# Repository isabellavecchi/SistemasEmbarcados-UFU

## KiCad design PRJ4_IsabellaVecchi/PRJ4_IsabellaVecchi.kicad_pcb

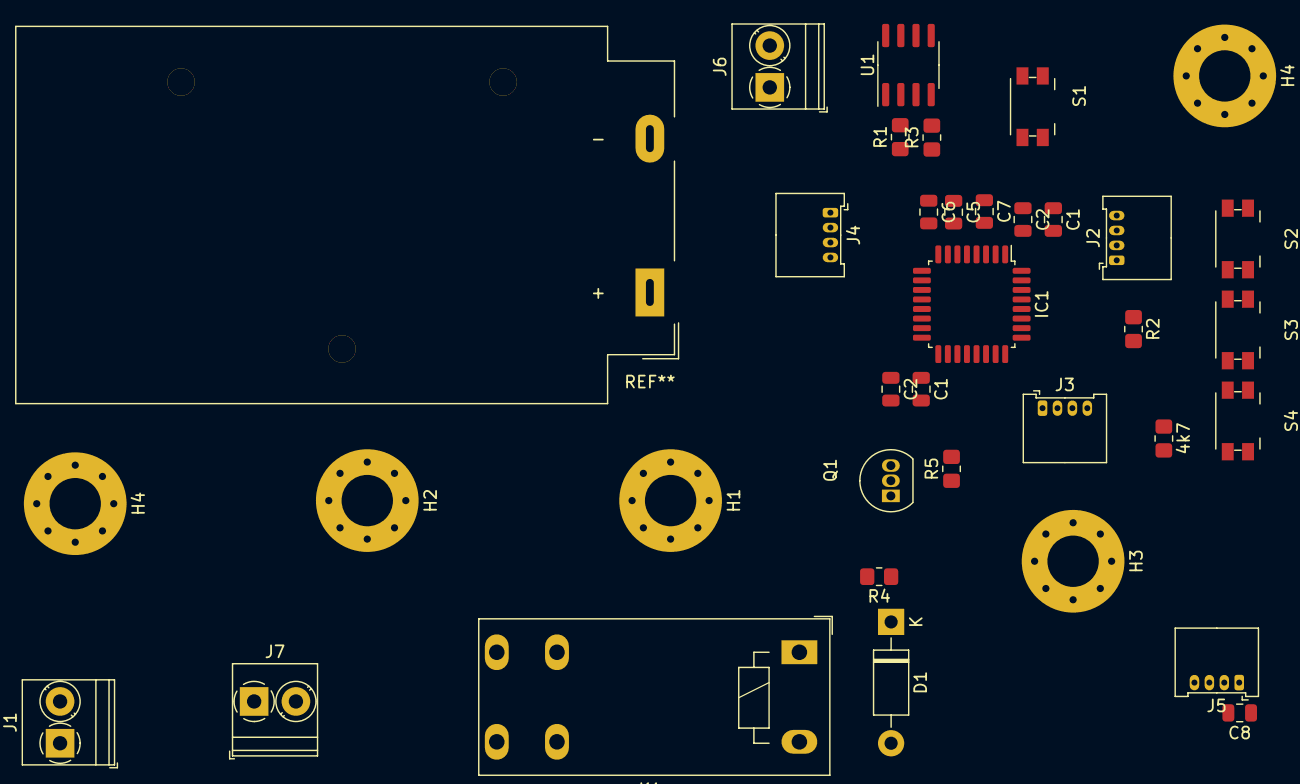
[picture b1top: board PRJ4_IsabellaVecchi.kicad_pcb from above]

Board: 2 copper layers, 35 parts (0 on the bottom side), 21 nets, no tracks yet.

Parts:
4k7: SMD R; R_0805_2012Metric_Pad1.20x1.40mm_HandSolder
C1, C1#2: 10uF; C_0805_2012Metric
C2, C2#2: 100nF; C_0805_2012Metric
C5: 1uf; C_0805_2012Metric
C6: 100nf; C_0805_2012Metric
C7: 0.1uf; C_0805_2012Metric
C8: 100n; C_0805_2012Metric
D1: 1N4001; D_DO-41_SOD81_P10.16mm_Horizontal
H1, H2, H3, H4, H4#2: MountingHole_Pad; MountingHole_4.3mm_M4_Pad_Via
IC1: STM32L052K8T6; LQFP-32_7x7mm_P0.8mm
J1: TerminalBateria; TerminalBlock_Phoenix_PT-1,5-2-3.5-H_1x02_P3.50mm_Horizontal
J2: Display_OLed; Molex_PicoBlade_53048-0410_1x04_P1.25mm_Horizontal
J3: ST-Link; Molex_PicoBlade_53048-0410_1x04_P1.25mm_Horizontal
J4: Terminal_SensorUmidadeTerra; Molex_PicoBlade_53048-0410_1x04_P1.25mm_Horizontal
J5: Terminal_SensorAmbiente; Molex_PicoBlade_53048-0410_1x04_P1.25mm_Horizontal
J6: TerminalPilha; TerminalBlock_Phoenix_PT-1,5-2-3.5-H_1x02_P3.50mm_Horizontal
J7: Válvula Solenoide; TerminalBlock_Phoenix_PT-1,5-2-3.5-H_1x02_P3.50mm_Horizontal
K1: RT44xxxx; Relay_DPST_Schrack-RT2-FormA_RM5mm
Q1: pnp TO-92 BC307; TO-92_Inline
R1: SMD 220R; R_0805_2012Metric_Pad1.20x1.40mm_HandSolder
R2: 10kR; R_0805_2012Metric_Pad1.20x1.40mm_HandSolder
R3: SMD 361R; R_0805_2012Metric_Pad1.20x1.40mm_HandSolder
R4, R5: SMD R; R_0805_2012Metric_Pad1.20x1.40mm_HandSolder
S1, S2, S3, S4: btSwitch; Panasonic_EVQPUK_EVQPUB
U1: LM317L_SO8; SOIC-8_3.9x4.9mm_P1.27mm

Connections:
5V: J6.1, U1.1 (VI)
12V: J1.1, K1.14, K1.24
BOOT0: IC1.31 (BOOT0), R2.1
BtMais: IC1.28 (PB5), S2.2 (COM)
D0-A: IC1.19 (PA9), J5.3 (D0)
D0-T: IC1.8 (PA2), J4.3 (D0)
Dp_SCL: IC1.29 (PB6), J2.3 (SCL)
Dp_SDA: IC1.30 (PB7), J2.4 (SDA)
GND: C1.2, C2#2.2, C5.2, C6.2
GND_bat: J1.2, J7.2
NRST: C7.2, IC1.4 (NRST)
unnamed: D1.2 (A), K1.A2, Q1.1 (C)
unnamed: D1.1 (K), K1.A1, R4.1
unnamed: J7.1, K1.11
unnamed: R1.1, R3.2, U1.4 (ADJ)
ST_SCL: IC1.24 (PA14), J3.3 (SWCLK)
ST_SDA: IC1.23 (PA13), J3.1 (SWDIO)
VDA: 4k7.1, C1.1, C1#2.2, C2.2, C2#2.1, C5.1, C6.1, C7.1, C8.2, H1.1, H2.1, H3.1, H4.1, IC1.5 (VDDA), IC1.16 (VSS_1), IC1.32 (VSS_2), J2.1 (GND), J3.2 (GND), J4.2 (GND), J5.2 (GND), J6.2, Q1.2 (E), Q1.3 (B), R2.2, R3.1, R5.1, S1.1 (COM_1)
VDD: C1#2.1, C2.1, C8.1, IC1.1 (VDD_1), IC1.17 (VDD_2), J2.2 (VCC), J3.4 (VCC), J4.1 (VCC), J5.1 (VCC), R1.2, R4.2, S2.1 (COM), U1.2 (VO), U1.3 (VO), U1.6 (VO), U1.7 (VO)
ValvulaSolenoide_pin: IC1.21 (PA11), R5.2
btGND: 4k7.2, S3.2 (COM_2), S4.2 (COM_2)

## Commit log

2023-04-11 pra mexer no outro pc
2023-06-16 Atualizando o Repositório
    Acabou que na correria esqueci de atualizar o git... Rsrs.
    A partir da tarefa1, começamos a utilizar a ferramenta STMcubeIDE, daí toda a evolução está comprimida no arquivo lab11 =D
2023-06-16 renomeando pasta
    até o lab11 já aprendemos sobre:
    - as diferentes configurações GPIO, tanto eletrônicas quanto em código;
    - a programar por Interrupção;
    - modo sleep;
    - UART
2023-06-20 adicionando codigo para timer
2023-06-26 um tapinha na organizacao hierarquica dos arquivos
    preparando o terreno para replicar o laboratorio para o trabalho final
2023-06-28 modelando a placa
2023-06-30 thinking about heat dissipation - pensando na dissipação de calor
2025-01-29 removing duplicated folder
